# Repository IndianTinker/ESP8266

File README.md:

# ESP8266
My Experiments with everyone's favorite Wifi Module

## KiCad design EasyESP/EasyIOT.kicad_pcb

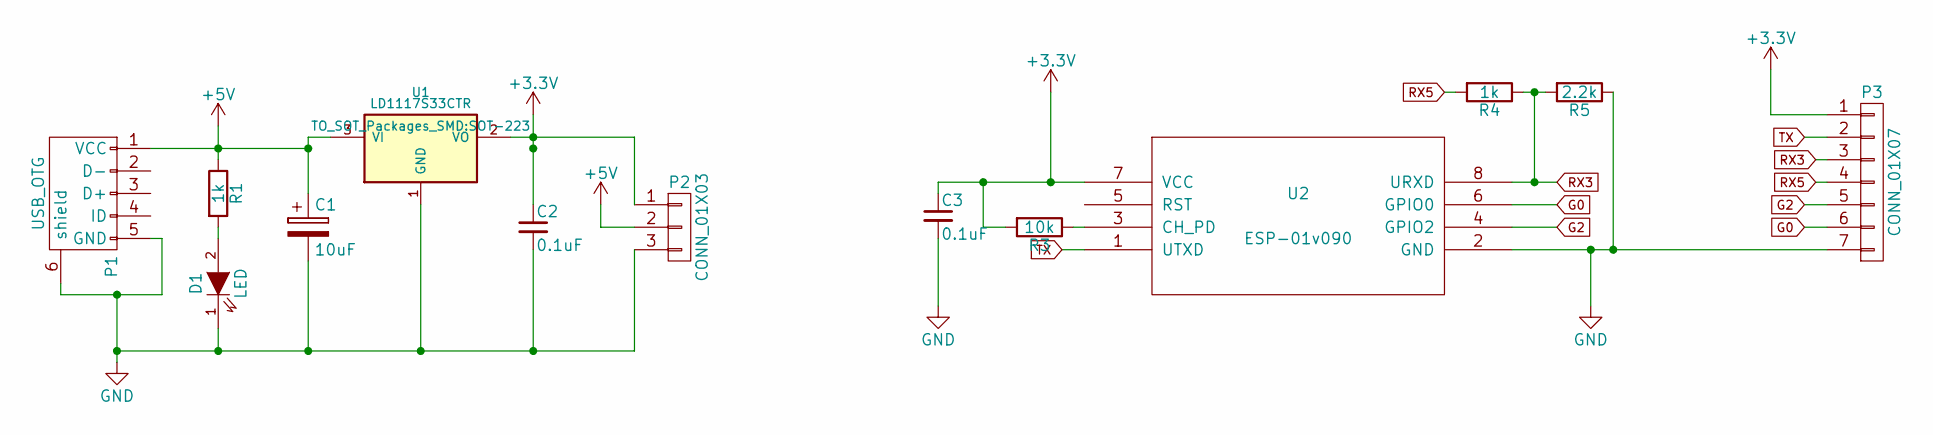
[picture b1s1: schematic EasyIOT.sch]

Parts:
C1: 10uF; Elko_vert_11.2x6.3mm_RM2.5
C2, C3: 0.1uF; C_0805
D1: LED; LED-0805
P1: USB_OTG; USB_Micro-B
P2: CONN_01X03; Pin_Header_Straight_1x03
P3: CONN_01X07; Pin_Header_Straight_1x07
R1, R4: 1k; R_1206_HandSoldering
R3: 10k; R_1206_HandSoldering
R5: 2.2k; R_1206_HandSoldering
U1: LD1117S33CTR; SOT-223
U2: ESP-01v090; ESP-01

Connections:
+3V3: C2.1, C3.1, P2.1, P3.1, R3.2, U1.2 (VO), U2.7 (VCC)
+5V: C1.1, P1.1 (VCC), P2.2, R1.1, U1.3 (VI)
G0: P3.6, U2.6 (GPIO0)
G2: P3.5, U2.4 (GPIO2)
GND: C1.2, C2.2, C3.2, D1.1 (K), P1.5 (GND), P1.6 (shield), P2.3, P3.7, R5.1, U1.1 (GND), U2.2 (GND)
unnamed: D1.2 (A), R1.2
unnamed: R3.1, U2.3 (CH_PD)
RX3: P3.3, R4.1, R5.2, U2.8 (URXD)
RX5: P3.4, R4.2
TX: P3.2, U2.1 (UTXD)

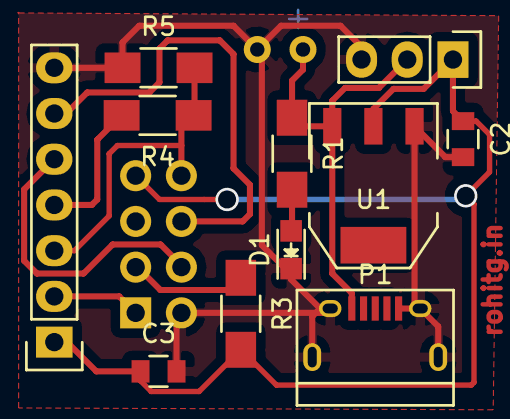
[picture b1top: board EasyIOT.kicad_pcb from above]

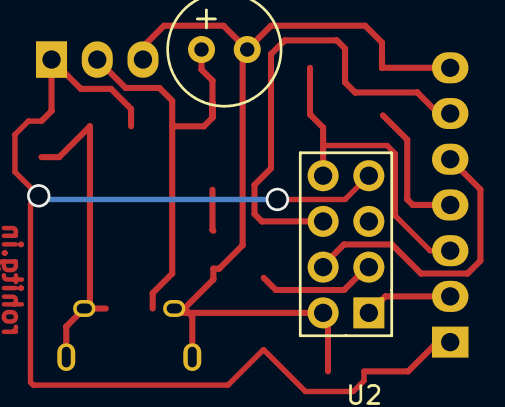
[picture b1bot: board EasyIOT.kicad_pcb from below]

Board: 2 copper layers, 13 parts (2 on the bottom side), 10 nets.

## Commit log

2015-10-20 Thingsend
2016-03-24 Easy Board added
